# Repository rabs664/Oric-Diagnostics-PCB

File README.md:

# Oric Diagnostics PCB
This is a reproduction of Mike Brown's Oric Diagnostic board and loopback harnesses, see [Mike Brown's Diagnostic ROM and PCB](https://oric.signal11.org.uk/html/diagrom.htm)

>[!NOTE]
>Acknowledgements go to Mike Brown for posting the original design to his excellent website [Oric And Atmos Support](https://oric.signal11.org.uk/index.htm). Many Thanks.

>[!CAUTION]
>USE AT YOUR OWN RISK.
>There is always the risk that the Oric Diagnostic board could cause harm to your Oric. Although I have tested the Oric Diagnostic board, there is no guarantee that it
>will work properly under all circumstances.

# Repository Content
This repository contains the KiCad and gerber files associated with the Diagnostic board and loopback harnesses.

# Changes from Mike Brown's Original Design
The following changes have been made from Mike Brown's Original Design:

* The clock circuit has been replaced by an [ECS-100AX-010](https://www.digikey.co.uk/en/products/detail/ecs-inc/ECS-100AX-010/827230) oscillator.

* The LED resistors have been replaced with 220ohm values.
>[!TIP]
>I still found the LEDs quite bright and you may consider increasing this value.

* LS components replaced with HCT.

* 3M holes have been added to allow for standoffs to be fitted.

For all other information about Mike Brown's original design please refer to [Mike Brown's website](https://oric.signal11.org.uk/html/diagrom.htm)

# Ribbon Cable
The Oric Diagnostic board has been designed to be used with a 34-way ribbon cable and can be used partly when the Oric motherboard is still in the case, altough it is a bit difficult to use the NMI button underneath.

However for the most part it will probably be used when the Oric motherboard has been removed from the case, but remember the motherboard is normally upside down and hence the twist in the ribbon cable when used in this configuration.

>[!TIP]
>Note the orientation of the ribbon connectors and red cable aligned to pin 1 and check connectivity back to the Oric motherboard before use.

# Port A Loopback
The Port A loopback is designed to fit straight into the Oric printer port.

>[!TIP]
>I found it difficult to remove the Port A Loopback when required. In the end I placed a pin header on the wrong side of the PCB and connected using a ribbon cable.
>
> 

# Keyboard Loopback
The Keyboard loopback is designed to fit over the end 10 pins.

>[!NOTE]
>I struggled to find pin headers that fitted. In the end I used these [pin headers](https://www.digikey.co.uk/en/products/detail/samtec-inc/SSA-110-S-T/1105806) but they are not a perfect fit.

# Casette Loopback
The Casette loopback is not part of this repository please refer to [Mike Brown's Diagnostic ROM and PCB page](https://oric.signal11.org.uk/html/diagrom.htm)

# 1MHz Clock
>[!NOTE]
>I have not had a need to use the clock source yet.

# ROM
Please refer to [Mike Brown's Diagnostic ROM and PCB page](https://oric.signal11.org.uk/html/diagrom.htm)

>[!NOTE]
>I used a 27C512 EPROM and copied the 16K ROM image four times to fill the 64K EPROM.

# Jumpers
Please refer to [Mike Brown's Diagnostic ROM and PCB page](https://oric.signal11.org.uk/html/diagrom.htm)

>[!CAUTION]
>I have not tested the jumpers A14=0, A15=0, INHIBIT VIA and VIA SEL

# Testing
The Oric Diagnostic board has been tested on two Oric-1 computers. One Oric-1 passed all tests and the other failed on the Casette Input test (which was resolved by replacing the LM358 OpAmp). So unfortunately I have not yet had to use the Oric Diagnostic board extensively on a fully failed computer.

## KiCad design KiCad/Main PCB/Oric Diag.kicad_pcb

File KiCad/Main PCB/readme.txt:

This folder contains the KiCad Project and gerbers for the main Oric Diganostic PCB.

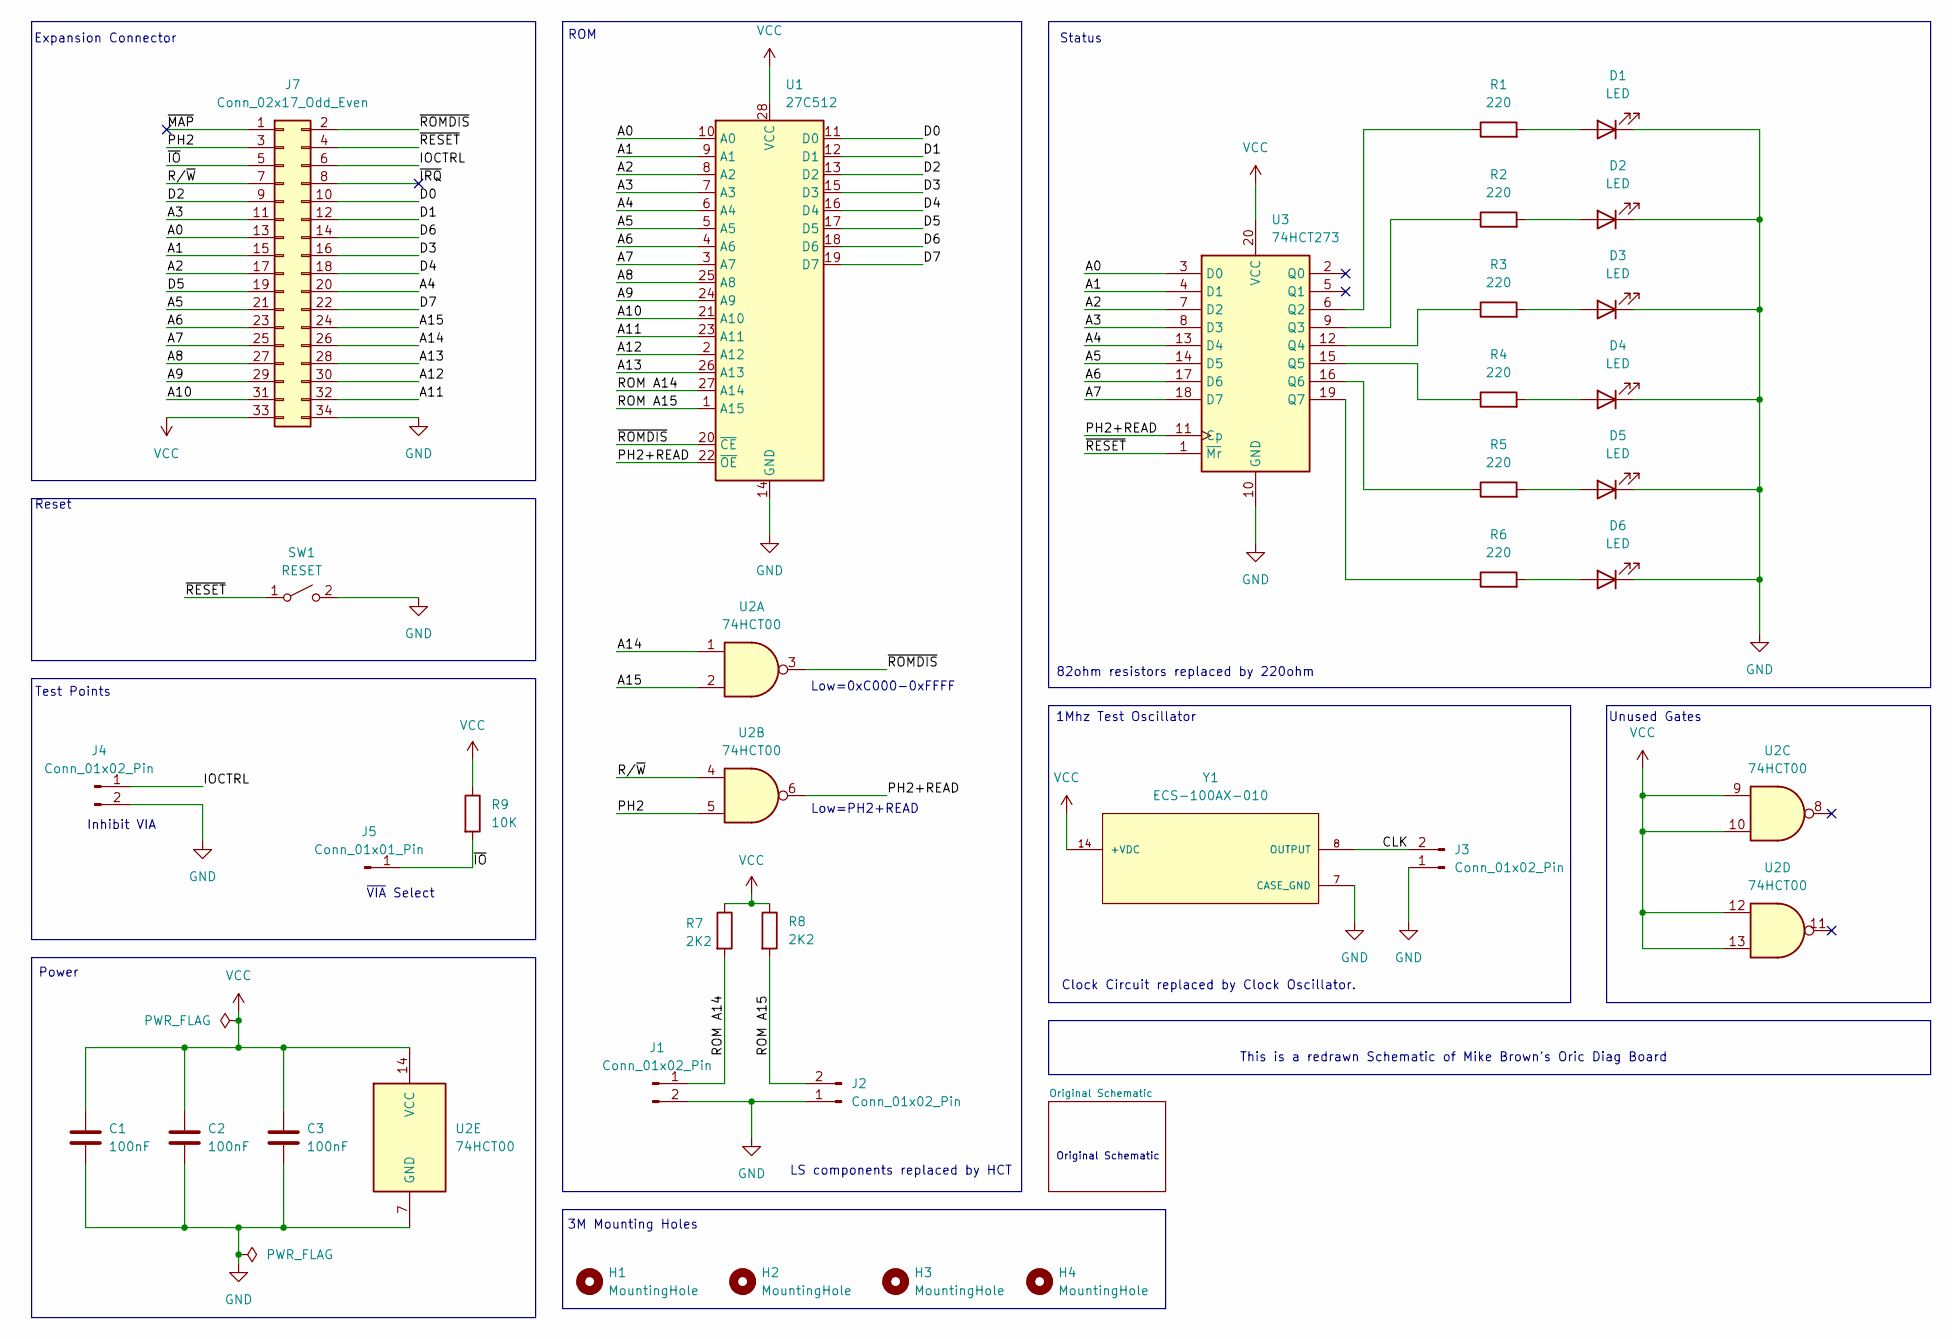
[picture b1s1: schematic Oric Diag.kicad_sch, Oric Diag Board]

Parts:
C1, C2, C3: 100nF; C_Disc_D5.0mm_W2.5mm_P5.00mm
D1, D2, D3, D4, D5, D6: LED; LED_D3.0mm
H1, H2, H3, H4: MountingHole; MountingHole_3.2mm_M3
J1, J2, J3, J4: Conn_01x02_Pin; PinHeader_1x02_P2.54mm_Vertical
J5: Conn_01x01_Pin; PinHeader_1x01_P2.00mm_Vertical
J7: Conn_02x17_Odd_Even; IDC-Header_2x17_P2.54mm_Vertical
R1, R2, R3, R4, R5, R6: 220; R_Axial_DIN0207_L6.3mm_D2.5mm_P7.62mm_Horizontal
R7, R8: 2K2; R_Axial_DIN0207_L6.3mm_D2.5mm_P7.62mm_Horizontal
R9: 10K; R_Axial_DIN0207_L6.3mm_D2.5mm_P7.62mm_Horizontal
SW1: RESET; SW_PUSH_6mm_H9.5mm
U1: 27C512; DIP-28_W15.24mm
U2: 74HCT00; DIP-14_W7.62mm_Socket
U3: 74HCT273; DIP-20_W7.62mm
Y1: ECS-100AX-010; OSC_ECS-100AX-010

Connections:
/A0: J7.13, U1.10 (A0), U3.3 (D0)
/A1: J7.15, U1.9 (A1), U3.4 (D1)
/A2: J7.17, U1.8 (A2), U3.7 (D2)
/A3: J7.11, U1.7 (A3), U3.8 (D3)
/A4: J7.20, U1.6 (A4), U3.13 (D4)
/A5: J7.21, U1.5 (A5), U3.14 (D5)
/A6: J7.23, U1.4 (A6), U3.17 (D6)
/A7: J7.25, U1.3 (A7), U3.18 (D7)
/A8: J7.27, U1.25 (A8)
/A9: J7.29, U1.24 (A9)
/A10: J7.31, U1.21 (A10)
/A11: J7.32, U1.23 (A11)
/A12: J7.30, U1.2 (A12)
/A13: J7.28, U1.26 (A13)
/A14: J7.26, U2.1
/A15: J7.24, U2.2
/CLK: J3.2, Y1.8 (OUTPUT)
/D0: J7.10, U1.11 (D0)
/D1: J7.12, U1.12 (D1)
/D2: J7.9, U1.13 (D2)
/D3: J7.16, U1.15 (D3)
/D4: J7.18, U1.16 (D4)
/D5: J7.19, U1.17 (D5)
/D6: J7.14, U1.18 (D6)
/D7: J7.22, U1.19 (D7)
/IOCTRL: J4.1, J7.6
/PH2: J7.3, U2.5
/PH2+READ: U1.22 (~OE), U2.6, U3.11 (Cp)
/ROM A14: J1.1, R7.2, U1.27 (A14)
/ROM A15: J2.2, R8.2, U1.1 (A15)
/R/~W: J7.7, U2.4
/~IO: J5.1, J7.5, R9.2
/~IRQ: J7.8
/~MAP: J7.1
/~RESET: J7.4, SW1.1 (A), U3.1 (~Mr)
/~ROMDIS: J7.2, U1.20 (~CE), U2.3
GND: C1.2, C2.2, C3.2, D1.1 (K), D2.1 (K), D3.1 (K), D4.1 (K), D5.1 (K), D6.1 (K), J1.2, J2.1, J3.1, J4.2, J7.34, SW1.2 (B), U1.14 (GND), U2.7 (GND), U3.10 (GND), Y1.7 (CASE_GND)
unnamed: D1.2 (A), R1.2
unnamed: D2.2 (A), R2.2
unnamed: D3.2 (A), R3.2
unnamed: D4.2 (A), R4.2
unnamed: D5.2 (A), R5.2
unnamed: D6.2 (A), R6.2
unnamed: R1.1, U3.6 (Q2)
unnamed: R2.1, U3.9 (Q3)
unnamed: R3.1, U3.12 (Q4)
unnamed: R4.1, U3.15 (Q5)
unnamed: R5.1, U3.16 (Q6)
unnamed: R6.1, U3.19 (Q7)
VCC: C1.1, C2.1, C3.1, J7.33, R7.1, R8.1, R9.1, U1.28 (VCC), U2.9, U2.10, U2.12, U2.13, U2.14 (VCC), U3.20 (VCC), Y1.14 (+VDC)

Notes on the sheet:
1Mhz Test Oscillator
Power
Clock Circuit replaced by Clock Oscillator.
ROM
Low=0xC000-0xFFFF
Test Points
3M Mounting Holes
Reset
Unused Gates
Inhibit VIA
This is a redrawn Schematic of Mike Brown's Oric Diag Board
Original Schematic
LS components replaced by HCT
Expansion Connector
Low=PH2+READ
~{VIA} Select
82ohm resistors replaced by 220ohm
Status

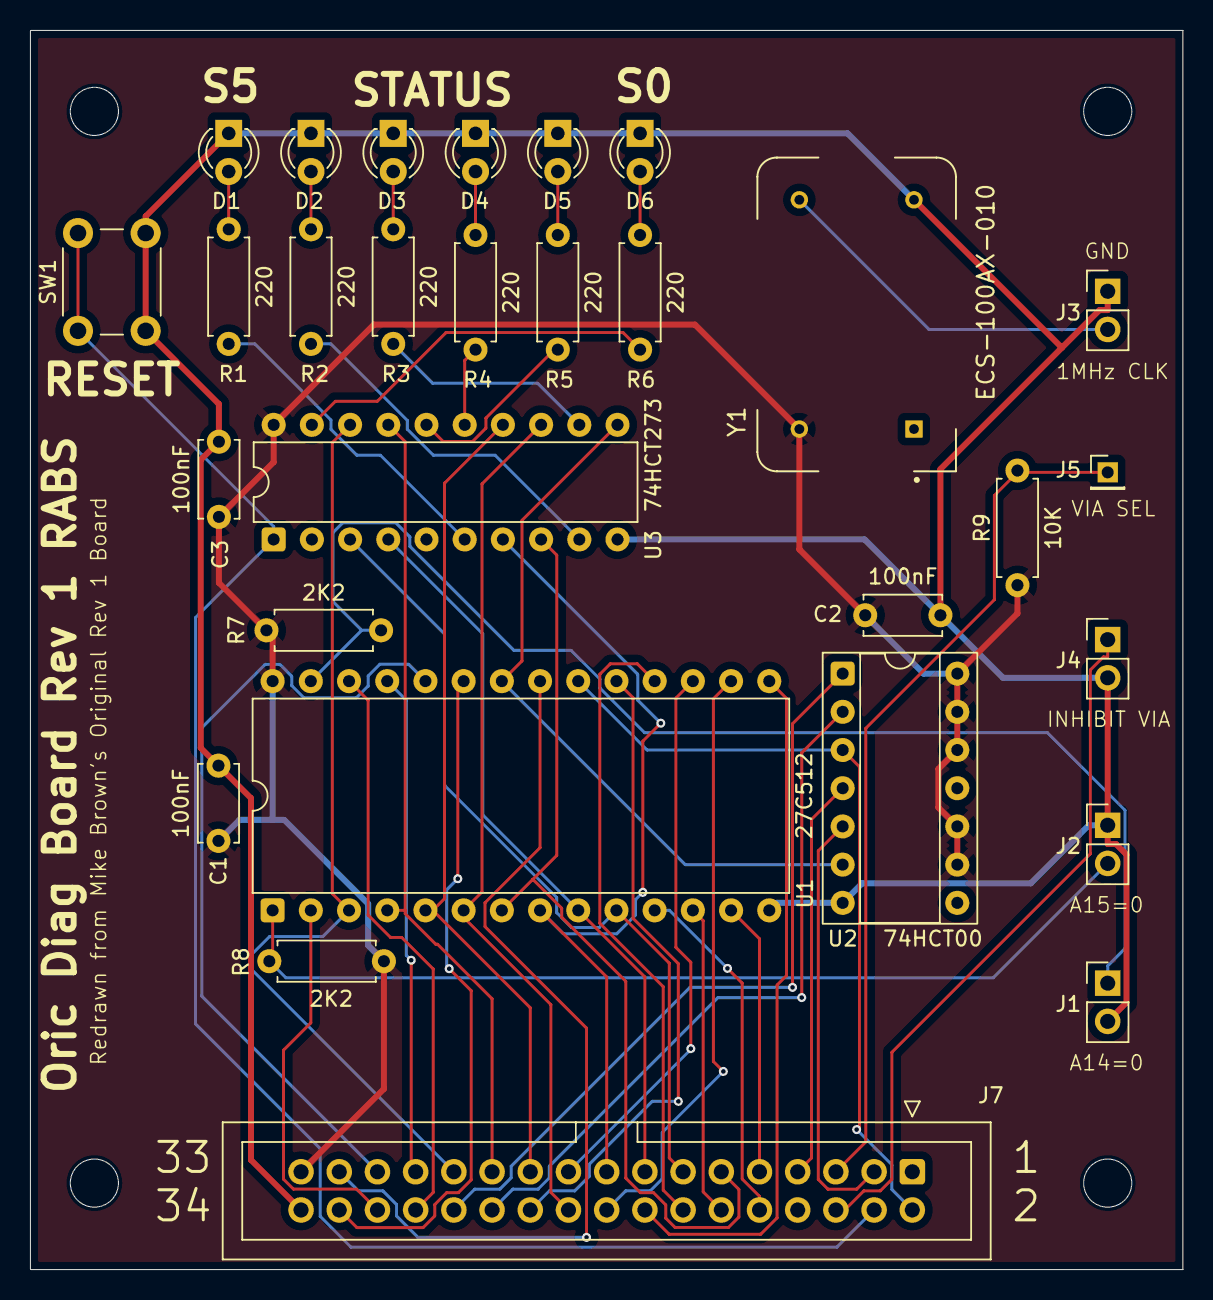
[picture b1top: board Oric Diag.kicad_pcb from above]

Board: 2 copper layers, 76.6 x 82.4 mm, 33 parts (0 on the bottom side), 48 nets.

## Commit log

2025-10-31 Add README for Oric Diagnostics project
    Added detailed information about the Oric Diagnostics project, including acknowledgements, repository content, and changes from the original design.
2025-10-31 Update README with ribbon cable usage details
    Added information about the ribbon cable usage with the Oric Diagnostic board, including orientation and configuration notes.
2025-10-31 Revise acknowledgements section in README
    Updated acknowledgements for clarity and improved wording.
2025-10-31 Replace Markdown image syntax with HTML tags
    Updated image links to use HTML img tags with specified widths.
2025-10-31 Fix typos and improve clarity in README.md
2025-10-31 Add readme for main Oric Diagnostic PCB
2025-10-31 Create readme for Port A Loopback PCB
    Added readme file for Port A Loopback PCB project.
2025-10-31 Add readme for Keyboard Loopback PCB project
2025-10-31 Create readme.txt for components directory
    Add readme file for components folder in KiCad project
2025-10-31 Update README with LS components replacement info
2025-10-31 Fix typos and formatting in README.md
    Corrected capitalization and punctuation in README.
